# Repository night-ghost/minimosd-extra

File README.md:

# minimosd-extra (russian is at the tail of this file)

Quickstart Guide (c) Johnex
----------------------
1. Download the latest MinimOSD-Extra build here: https://github.com/night-ghost/minimosd-extra/blob/master/osd_latest.zip?raw=true
2. Run the OSD_Config.exe
3. Connect your MinimOSD to your pc making sure you are using an FTDI that has 5V and not 3.3V.
4. After the usb driver is installed, select your COM port in OSD_Config.
5. Click Options -> Update Firmware. Select the latest MinimOsd_Extra_Uni.8XXDV-release.hex file from the "FW_+_Char" folder.
6. This firmware has a built in character set uploader, so just click Options -> Update CharSet. Select the latest character set MinimOSD_2.4.1.X.mcm from the "FW_+_Char" folder. Notice that this MimimOSD-Extra has a custom character set and must be updated if coming from another fork or the original, and some newer versions might require a new version, always check the "FW_+_Char" folder.
7. Set your video mode to Auto if you have different cam types, or select NTSC or PAL if you have just 1 cam and you know it's type or had issues with Auto.
8. Connect your OSD directly to a monitor or to a video transmitter so you can see the OSD output, making sure you don't forget to connect the antenna to the video transmitter before powering it on if you are using that. Click Options -> Load TLog. Select 2015-09-06 18-40-55.tlog from the "FW_+_Char" folder.
9. Set up the screens as you want. Click "Save Tab to OSD" and then click "Start" to run a simulation so you can see how everything looks without having to set up a copter. If something is not right, click "Stop", do the changes, save the config again and click "Start" again to see the new changes.
10. If you encounter that your screen is not centered, change the "Offsets", Left and Top from the config page. You can also move panels away from the edge if your screen gets cropped.

Description

* refactored a bit - now uses much less memory and can use less EEPROM

* also MAX7456 renew doing in VSYNC to get rid of "snow" on screen - like 
in http://forum.rcdesign.ru/f90/thread132831-195.html#post5602416 but on interrupt instead of polling via SPI.

* Also PSTR to all strings

* NEW FEATURES:

* 4 screens instead of 2

* individual control of sign icon of each panel per screen

* voltage, current & RSSI can be used from external pins

* TLOG player in configurator - now settings can be checked without working plane/copter!

* RADAR (like in MiniNAZAosd) and ILS in Horizon, can be enabled individually

* horizon angles can be adjusted, indepentently in PAL and NTSC

* PAL/NTSC detected dynamically - now can use different cameras!

* screen offsets via configurator

* can use additional pins (that can be found on some boards) for measuring 2nd battery current and voltage

* new GPS coords - in one line

* fixed a lot of old bugs of CT

* Any RC channel can be translated to output pin (eg. for cameras switch)

* Setup screen! Some parameters can be adjusted without computer - by RC 

* Panel in CT can be dragged over any point, not only for the upper left corner

* and much more! See [CHANGELOG.md](https://github.com/night-ghost/minimosd-extra/blob/master/CHANGELOG.md)

If you like this project and want to support further development - you can do it! USD
   EUR

changelog in [CHANGELOG.md](https://github.com/night-ghost/minimosd-extra/blob/master/CHANGELOG.md)
some descriptions are in [wiki](https://github.com/night-ghost/minimosd-extra/tree/master/wiki)

fonts:

MinimOSD_2.4.1.x.mcm         - base font
MinimOSD_2.4.1.x-digital.mcm - styled for 7-segment and dotted horizon

Attention! This version is incompatible with the tools from the ArduCam and original MinimOSD-extra!

Discussion forum - http://www.rcgroups.com/forums/showthread.php?t=2591835 (abandoned) http://www.ykoctpa.ru/groups/eye-in-a-sky/forum/topic/minimosd-english-support-thread/#post-9147

/* RUSSIAN */

Быстрый старт

1. Загрузите последнюю версию MinimOSD-Extra отсюда: https://github.com/night-ghost/minimosd-extra/blob/master/osd_latest.zip?raw=true
2. Запустите OSD_Config.exe
3. Подключите MinimOSD на ваш компьютер, убедившись, что вы используете FTDI с напряжением 5V, а не 3.3V.
4. После установки драйвера USB, выберите COM-порт в OSD_Config.
5. Нажмите кнопку Options -> Update Firmware. Выберите последнюю версию файла MinimOsd_Extra_Uni.8XXDV-release.hex из папки "FW_+_Char".
6. Эта прошивка имеет встроенный загрузчик знакогенератора, так что просто нажмите кнопку Options -> Renew CharSet. Выберите последний набор символов MinimOSD_2.4.1.X.mcm из папки "FW_+_Char". Обратите внимание на то, что этот MimimOSD-Extra имеет свой набор символов, и не будет работать с символами из других версий. Поэтому знакогенератор модуля должен быть обновлен, так что всегда проверяйте папку "FW_+_Char".
7. Установите режим видео на Auto, если у вас одновременно различные типы камер, или выбрать NTSC или PAL, если у вас есть только один камера, и вы знаете ее тип.
8. Подключите OSD непосредственно к монитору или видео передатчик, так чтобы увидеть вывод OSD, убедившись, что вы не забыли подключить антенну к видеопередатчику перед включением его. Нажмите кнопку Options -> Load TLOG. Выберите 2015-09-06 18-40-55.tlog из папки "FW_+_Char".
9. Настройте экраны, как вы хотите. Нажмите кнопку "Save Tab to OSD", а затем нажмите кнопку "Start", чтобы запустить моделирование. Теперь вы сможете увидеть как все выглядит на самом деле без необходимости подключать коптер/самолет. Если что-то не так, нажмите кнопку "Stop", сделайте изменения, сохраните конфигурацию и нажмите кнопку "Пуск" снова, чтобы увидеть новые изменения.
10. Если вы обнаружите, что ваш экран не по центру, то можете изменить "Offsets", слева и сверху, на вкладке конфигурации. Можно также перемещать панели подальше от края, если ваш экран обрезан.

Описание отличий

* Отрефакторил, убрав чудовищный расход памяти на хранение всех настроек всех возможных экранов сразу, также 
убрал "регистры" флагов (и все с ними связанное) в пользу хранения вместе с координатами. Ну и по 
мелочи - PSTR, PROGMEM и отказ от ненужных статических массивов. 

* В результате имеем свободных 721 байт вместо 160 в оригинале. 

* Также сделано обновление памяти MAX7456 во время VSYNC дабы избавиться от "снега" на экране из-за помех, по мотивам
http://forum.rcdesign.ru/f90/thread132831-195.html#post5602416 но через прерывание вместо странного поллинга 
через SPI.

* Также сделана регулировка отступов от края экрана через конфигуратор

** НОВЫЕ ВОЗМОЖНОСТИ!

* Объединены самолет и коптер, выбор производится по значению из EEPROM и может МЕНЯТЬСЯ НА ЛЕТУ!

* Уменьшен расход EEPROM в три раза (!). В результате можно задать 4 экрана вместо 2-х и при этом куча свободного места под новые параметры.

* Чтение-запись EEPROM в цикле а не индивидуальными байтами - нет больше длинных "портянок"

* Видимость иконок - обозначений каждой "панели" задается индивидуально, независимо по экранам

* Напряжения, токи и RSSI могут читаться с дополнительных выводов (со сглаживанием по 8 отсчетам),
источник и поправочные коэффициенты задаются в конфигураторе независимо

* Переключение экранов может производиться по внешнему PWM для использования с номерами каналов выше 8

* В авиагоризонте сделаны поправочные коэффициенты (независимые для PAL и NTSC), и добавлен "Радар" (по мотивам МиниНазаОСД). 

* Видимость Радара и ILS задается индивидуально.

* Изменена логика формирования "панелей", так что теперь мелкие панели могут использовать незадействованные области крупных панелей. 
Это позволило отрисовывать радар, ILS и центральный маркер в пределах авиагоризонта

* Переключение PAL/NTSC может производиться "на лету", без перезагрузки - позволяя использовать две камеры разных форматов

* в коде сделан отладочный HEX-дамп прямо на экран

* В конфигураторе сделан плеер TLOG - теперь можно проверить работу OSD без самолета/коптера.

* Смещение экрана относительно синхроимпульсов задается через конфигуратор

* Изменен шрифт для отображения всех новых вкусностей

* Сделан вариант отображения координат GPS в одну строку

* Добавлена возможность вывода любого канала наружу в PWM 

* После всего этого остается свободно 325 байт памяти и 2+к флеша.

* Экран настройки! До арма можно менять некоторые параметры без компьютера - просто с пульта

* Исправлено множество старых багов конфигуратора

* панель в конфигураторе можно таскать за любую точку а не только за левый верхний угол

* и многое другое - смотрите [историю версий](https://github.com/night-ghost/minimosd-extra/blob/master/CHANGELOG_RU.md)

Если вам понравился проект и вы хотите поддержать его дальнейшее развитие - вы можете это сделать 
 USD  
 RUB

история версий в файле [CHANGELOG_RU.md](https://github.com/night-ghost/minimosd-extra/blob/master/CHANGELOG_RU.md)

Шрифты:

MinimOSD_2.4.1.x.mcm         - основной фонт
MinimOSD_2.4.1.x-digital.mcm - стилизация под 7-сегментный индикатор и точечный горизонт

Внимание! Эта версия несовместима с утилитами из оригинальной MinimOSD!

некоторая документация есть в [wiki](https://github.com/night-ghost/minimosd-extra/tree/master/wiki).

Обсуждение - http://www.ykoctpa.ru/groups/eye-in-a-sky/forum/topic/minimosd-novaya-proshivka/

ЛИЦЕНЗИОННОЕ СОГЛАШЕНИЕ (честно потыренное у Ubilling)

Данный программный продукт (далее ПП) распространяется под лицензией GNU GPL v.2 с полностью открытым кодом и полностью бесплатно.
Так было всегда, так и останется. Без компромиссов. THIS IS SPARTA OPENSOURCE!!!
Обрекший себя на использование данного продукта принимает тот факт, что ему никто и ничего не должен.
Вообще никаких гарантий - ни явных ни подразумеваемых. Все работает так как работает.
Перед использованием ПП верующим рекомендуется поставить свечку в храме, атеистам - геморроидальную.
Мы не несем никакой ответственности за хаос, панику, разрушения и апокалипсис, возникшие в процессе эксплуатации. 
Если у вас возникли вопросы - потрудитесь почитать документацию. Если документация не дала ответов о смысле жизни - попробуйте спросить на форуме.
По умолчанию все баги являются фичами, если вы считаете что нашли багу - попробуйте ее использовать в повседневной жизни ну или расскажите нам.
Если у вас есть какая-то хотелка нужная строго вам - вы можете реализовать ее либо самостоятельно и сделать PR на гитхабе, 
либо заказать, либо продолжать хотеть. 
Это намек на то, что бесплатно работать фуллтайм на вас никто не вписывался.

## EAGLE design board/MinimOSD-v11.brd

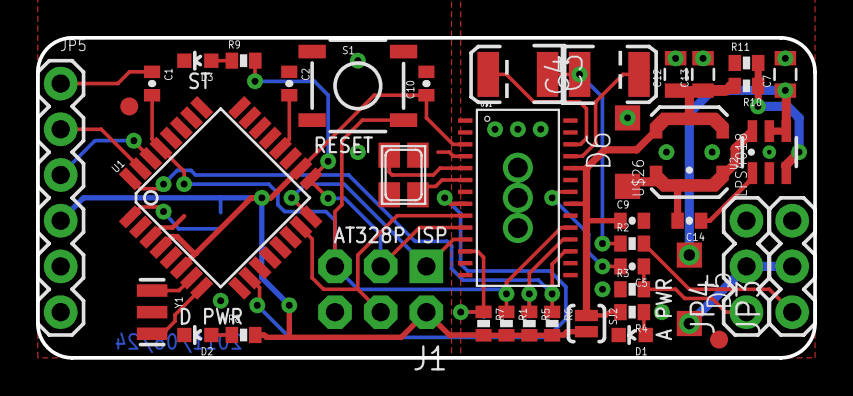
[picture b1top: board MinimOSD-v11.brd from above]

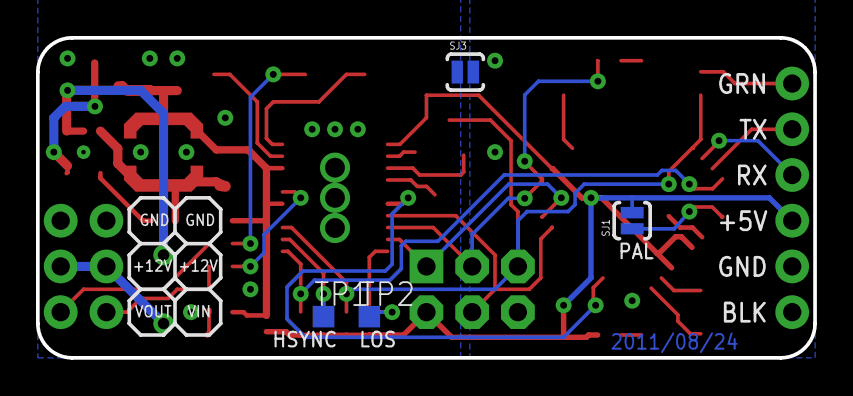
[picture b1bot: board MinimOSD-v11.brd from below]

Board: 4 copper layers, 43.2 x 17.8 mm, 45 parts (4 on the bottom side), 35 nets.

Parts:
C1, C2, C5, C9, C10: 0.1uF; 0402-CAP
C3, C4: 47uF; EIA3528
C7: 1uF; 0805
C12, C13: 4.7uF; 0805
C14: 0.15uF; 0402-CAP
D1, D2: RED; LED-0603
D3: YELLOW; LED-0603
D5: SOD123
D6: MA2YD26; SOD123
J1: AVR_SPI_PRG_6NS; 2X3-NS
JP1, JP2: FIDUCIAL1X2; FIDUCIAL-1X2
JP3, JP4: 1X03
JP5: 1X06
Q1: 27MHz; NX3225
R1: 10k; 0402-RES
R2, R3: 75; 0402-RES
R4, R8, R9: 330; 0402-RES
R5, R6, R7: 1k; 0402-RES
R10: 5.62k; 0402-RES
R11: 1.02k; 0402-RES
S1: TACTILE_SWITCH_SMD
SJ1, SJ2, SJ3: SOLDERJUMPERNO; SJ_2S-NO
TP1, TP2: TPTP12SQ; TP12SQ
U1: ATMEGA328P; TQFP32-08
U2: LM2842Y; MK06A
U$1: MAX7456; TSSOP28
U$26: LPS4018
Y1: 16MHz; RESONATOR-SMD

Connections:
5V: C10.1, J1.2, JP5.4, R1.2, R5.2, R6.2, R7.2, R8.2, SJ1.2, SJ2.2, U1.4, U1.6, U1.18, U$1.3
AGND: C7.2, C9.2, C12.2, C13.2, D1.C, D6.A, JP3.3, JP4.3, R3.1, R11.1, SJ3.1, U2.2, U$1.20, U$1.23
AVDD: C9.1, C12.1, C13.1, R4.2, R10.2, SJ2.1, U$1.21, U$1.24, U$26.B
DTR: C1.1, JP5.1
GND: C2.1, C10.2, D2.C, D3.C, J1.6, JP5.5, JP5.6, S1.1, S1.2, SJ3.2, U1.3, U1.5, U1.21, U$1.4, Y1.2
HSYNC: R5.1, TP1.TP, U$1.18
LOS: R7.1, TP2.TP, U$1.12
MISO: J1.1, U1.16, U$1.11
MOSI: J1.4, U1.15, U$1.9
unnamed: Q1.4, U$1.6
unnamed: C2.2, U1.20
unnamed: U1.7, Y1.1
unnamed: U1.8, Y1.3
unnamed: Q1.2, U$1.5
unnamed: C3.A, U$1.26
unnamed: C4.A, U$1.25
unnamed: C3.C, C4.C, R2.1
unnamed: C5.2, U$1.22
unnamed: D1.A, R4.1
unnamed: D2.A, R8.1
unnamed: D3.A, R9.1
unnamed: C7.1, D5.C, U2.4, U2.5
unnamed: C14.1, U2.1
unnamed: C14.2, D6.C, U2.6, U$26.A
unnamed: R10.1, R11.2, U2.3
PAL: SJ1.1, U1.1
RAW: D5.A, JP3.2, JP4.2
RESET: C1.2, J1.5, R1.1, S1.4, U1.29, U$1.19
RXI: JP5.3, U1.30
SCK: J1.3, R9.2, U1.17, U$1.10
SSOSD-IN: U1.10, U$1.8
TXO: JP5.2, U1.31
VIN: C5.1, JP4.1, R3.2
VOUT: JP3.1, R2.2
VSYNC: R6.1, U1.32, U$1.17

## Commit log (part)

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2014-03-13 New charset
2014-04-03 Copter: Home Alt -> Relative altitude (from VFR_HUD message) Alt -> GPS reported altitude
2014-04-21 CT Tool: Bug fix uploading charset in newer fw versions
2014-04-29 Copter: Only allow showing flight summary if traveled distance greater than 50 meters
2014-05-08 Copter added new flight modes: flip, auto tune, hybrid
2014-05-13 CT Tool: New automated CT Tool upgrade - In development
2014-11-27 -WP arrow fix for latest arduplane -Alt error fix on tune panel
2014-11-28 Added character uploading FW
2014-11-30 Edited wiki page Charset through web user interface.
2015-02-03 Before transfer to GIT
2015-04-02 added usage of auxilary input pins int in lot of places replaced with uint8_t some font redesign and new visual elements
2015-04-02 updated font and compiled .HEX
2015-04-07 refactored configurator! No more '30', '18' and other mystical numbers - they are now global constants. Number of screens can be easily changed via 'npanels' without any code change. Removed "generat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
2015-04-09 first step of EEPROM reorganization
2015-04-21 now it works!
2015-04-23 RADAR from naza osd
    new cool fonts
2015-04-24 screen offsets now a via config tool
2015-04-27 final clearance
2015-07-10 PAL/NTSC live change now working!
    removed BUG with GPS2 panel
2015-07-15 readme changed
2015-10-15 enabled translation of PWM from RC6-RC8 to external pin
2015-12-13 fixed bug with formatting in configuration applet Flight results panel now can be on any screen Class SingleSerial - uses ~500 bytes less flash than FastSerial other space optimizations - now free 4,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
    в конфигураторе исправлен баг с форматированием
    панель сводки сделана равноправной и ее можно назначить на любой экран
    Класс SingleSerial - на ~500 байт меньше чем FastSerial
    прочая оптимизация размера кода - теперь свободно 4.5к флеша
2015-12-28 serial buffer counters reduced to uint8_t
2016-01-28 PWM output working! binary recompiled with GCC 5.3
2016-01-28 decorative removal of old code
2016-01-29 now it compiles
2016-01-29 proportional increment in setup
2016-01-30 OSD_Config rebuild by MS VS
2016-02-01 fixed bug with "long distances" display
2016-02-02 adding NOINLINE to some functions saves ~400 bytes
2016-02-02 fixed CT startup bug
2016-02-24 working SETUP & fixed bugs
2016-02-26 automatic UAVtalk IDs generation
2016-03-09 v813:
    HUD borders can be turned off
    RADAR point can show track (3 points) - requires charset 2.4.1.2
    RSSI values now is 2 bytes and has no 255 limit
2016-03-11 created manlink-only HEX MinimOsd_Extra_Uni.813DV-MAVlink-release.hex
2016-03-13 v814
    fixed bug "no input data"
    fixed wrong pitch
2016-03-16 v815
    fixed bug with battery panel sizes
2016-03-18 default panel's placement changet to panels don't overlaps
2016-03-18 corrected CRC issue in UAVtalk more space optimizations
2016-03-23 support for new APM_Plane modes - quad-plane new parameters in Setup screen much more space optimizations preliminary support for AutoQuad MAVlink dialect preliminary support for CleanFlight/MWII pro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
2016-03-24 v816:
    Walkera telemetry output (for DEVO RX705/RX707 receivers) now working!
    Support of CleanFlight/MWII protocol (untested)
    Support of AutoQuad's MAVlink dialect (untested)
    support for new APM_Plane modes for quad-plane
2016-03-25 filtered out GCS messages, translated by Copter 3.3+ and plane 3.4+
2016-03-26 fixed small bug in MAVlink handling
2016-03-27 binaries for v817
2016-03-28 do it compiles via MAKE
2016-03-29 changed logick of calculation of battery percentage
2016-03-29 Single Serial Submodule Updated Command: git submodule update --remote --merge
2016-03-30 v819
2016-03-30 CT: removed MsgBox'es from EEPROM utils CT: TLig player stops when COMport used
    removed delay() in setup()
2016-04-01 v821 * fixed buk with NTSC in CT * better UAVtalk & mwii syncronization * PWM_IN interrupt enabled only if used * some cleanup * ZIP file for download all needed
2016-04-02 v823 * add new flag to all panels that turns on "alternate" mode for some panels * WindSpeed, Airspeed and Groundspeed in Alternate mode shows speed on m/s instead of km/h * new charset to show m/s
2016-04-05 Quick Start on Readme
2016-04-08 v826
    * MAVlink message scrolled if length more than screen width
2016-04-10 Update README.md
    Fix latest link.
2016-04-13 some changes in CT Settings tab
2016-04-18 v828
    * sensor has "pulse mode" checkbox
    * some optimizations
2016-04-19 some bugfixes with RSSI in CT
2016-04-22 created DEBUG version
2016-04-25 v831
    * screen switch in rotation mode can be done only once
2016-05-10 v833
    * reserved space for sign for climb rate
2016-05-13 rename 'FW & Char' folder to 'FW_+_Char'
2016-05-13 v836 * support for LTM telemetry protocol (untested)
2016-05-17 * fixed bug with Message panel
2016-05-20 v839 * fixed Vertical Speed panel broken in v838
2016-05-23 changes in Readme
2016-05-25 * panelRose modification
2016-05-26 v842 * one good man from GCC team told me two "secret" (not mentioned in GCC --help) optimization flags so we now has ~1Kbyte of free space! * thanks above - added 2nd, 3rd and 4th alternate checkbox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
2016-05-27 v843 * 3DR modem RSSI can be used as RSSI source * additional fields in flight results - current, vertical speed up & down * support for GPS-less setup: Alt and Groundspeed works without GPS * flight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
2016-05-30 v845 * fixed bug in ChannelStatus panel * CT clears message after 10s
2016-05-30 * fixing panHDOP and panGPSats
2016-06-01 v847 * fixed NTSC inconsistency with the CT * removed % from panRSSI in CT * added ability to exclude MAVlink from build * all telemetry protocol's files moved to 'protocols' folder * fixed panel siz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
2016-06-02 uploaded CT sources
2016-06-03 added debug version
2016-06-05 Add buttons to clear a screen and copy another screen.
2016-06-07 Add ui_mode to Panels
2016-06-09 fixed bug in CT with reading panel Scale from OSD
2016-06-09 Reorganize X and Y UI controls
2016-06-10 fixed bug with flickering panels
2016-06-10 again fixed framerate bug
2016-06-14 v853 * strings now are working! And Channel State panel uses first 5 of them
2016-06-15 v856 *fixed bug with panel's properties visibility
2016-06-21 v857 * fixed bug with panel selection in CT * complementary filter of panEff changed from 1/10 to 1/100 * a try to change Horizon behavior for large banks (>70grad) * minor fixes
2016-06-29 * ILS now allows plane to come to runway from opposite direction * fixed bug in ILS with HUD size * when landing margers are not visible ILS now show arrows to help find smaller turn * some size opti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
2016-07-01 v858 * fixed some CT bugs * localisation support! lang.txt file in EXE's folder, * support of timed screen switch (untested) * file default.osd loaded at startup if present * fixed bug with reverse R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
2016-07-01 v860 * MAVLink don't loses sync on CRC errors * time counted for "no data" state
2016-07-04 v861 * some bugfixes
2016-07-05 * fixed stick direstions in Setup * fixed sensors in Setup
2016-07-12 v865 * calculates adequate stream rate for current COM-port baudrate. * detects overloaded datastreams and (if TX connected) tries to re-request them at less rate. * minor fixes * CT shows TLOG time
2016-07-13 v867 * reversed roll in horizon AKA Russian HUD
2016-07-18 v869 * support for copter's Brake and Throw modes
2016-07-20 v870 * unknown new modes shown as numbers but not as screen garbage
2016-07-25 v872 * added detected port speed to "no data" screen
2016-07-27 added MinimOsd_Extra_Uni.873DV-MAVLINK-release.with_bootloader.hex
2016-08-01 v875 * UAVtalk works again! * fixed underflow bug in panRose * fixed lagre pitch horizon behavior
2016-08-04 v876 * UAVtalk uses BaroAlt when no GPS. * fixed flight time counting * fixed RussianHUD on startup screen
2016-08-09 v877 * new Power panel which shows mean consumed power (smoothing by complementary filter 1:10) * maximal power added to flight results (FlightData panel) * all complementary filters are unified * tr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
2016-08-22 v879 * fixed Voltage and Altitude for UAVtalk * added Temperature (by Baro) for UAVtalk * if MAX7456 loses VSYNC interrupts then OSD switch to old-style refresh by timer - snow on scren is better tha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
2016-08-23 Add files via upload
    -Direction arrows redraw
    -Some changes to dashes in horizon symbols
2016-08-29 * README.md split to README.md,CHANGELOG.md and CHANGELOG_RU.md * all the above files copied to Released folder on each commit
2016-09-01 * added UAVTalk-debug binary
2016-09-05 Coding style issues
    - Removing trailing whitespaces.
    - Tabs converted to whitespaces.
2016-09-10 Revert "Fix NTSC Designer"
    This reverts commit a6b417d5ab8283d063f37c9141e0aaba490aca9d.
2016-09-10 remove usage of PAL related variables
2016-09-17 commited right version of CT
2016-09-20 try to upload
2016-09-28 small typo fix
2016-10-03 added HEX with Walkera telemetry support - MinimOsd_Extra_Uni.887DV-MAVLINK+Walkera-release.hex
2016-10-12 added License in Russian part of Readme
2016-10-21 v890 * added recent MAVlink 1.0 massages * new panels - date & time. Works only in recent ArduPilot versions! * panel Home Direction now has a angle in numerical form * added filter to RSSI panel * a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
2016-11-03 a little black magic - and we again have ~300 bytes of a free flash. Magic can be seen in compat.h
2016-11-08 Variometer panel sample in CT
2016-11-11 updated CT to support 3000 RSSI value
2016-11-13 v897 * fixed efficiency
2016-11-13 added issue template
2016-11-17 v901 * added "*4" checkbox to variometer
2016-11-18 dropped packet count changed from 5 to 10
2016-11-18 903 * fixed bug with vario zero position
2016-11-24 v905 * fixed NTSC horizon bug * added checkbox in RadarScale to select UAV arrow direction
2016-12-07 v807 - TEST VERSION! * removed usage of nested interrupts
2016-12-08 v909 * fixed bug with MAVlink message
2016-12-13 v911 - THE TEST VERSION!!! * another try to work on myairbot's board and not spoil regular boards
2016-12-27 v913 *added new panel - motors output
2016-12-30 v914 * separated panels for coordinates Lat and Lon
2017-01-12 v916 * panAlt can use alternate altitude source
2017-01-14 v918 * a try to run on airbot's board - thanks vierfuffzig!
2017-03-20 v921 * fixed bug in parsing MAV_BATTERY2 message
2017-03-21 v923 fixed size issue
2017-03-24 rebuilt binaries
2017-03-27 v925 * font uploader moved out from main firmware. Use Character_Updater_FW.hex instead. * HeartBeat packets generated only if 3DR RSSI selected
2017-04-06 v927 * added EEPROM reading via MAVlink * fixed bug with "Reading param 12" in MP
2017-04-16 v930 * fixed startup hang from v929
2017-04-27 add binariy for 644
2017-04-27 v931 * added baudrate setting for NMEA protocol
2017-05-02 v932 * debug version
2017-05-05 added support for 2nd UART on ATmega644
2017-05-06 Added by200 rotation functionality.
    this is a way overdue port of my patch to the original minimosd-extras:
    https://github.com/diydrones/MinimOSD-Extra/compare/master...marcmerlin:remove_ms_rot?expand=1
    I had to disable USE_AUTOSWITCH code due to the code size issue.
    Feel free to re-enable and disable/remove something else.
    Technically my code makes the mode switch rotation code obsolete,
    because you can use it instead of the mode switch detection, and it
2017-05-07 Revert some changes for an easier merge with upstream.
2017-05-10 fixed wp distance
2017-05-11 v935
    * \r\n\ for NMEA protocol
2017-06-04 Fix some issues and errors I found
    NMEA.h still do not work correct and do not shows correct Lan/Lon and are not usable.
    It seems function "GPS_calc_longitude_scaling()" do not work correct too.
2017-06-09 LAT and LON are corected
2017-06-20 v938 * Preliminary support for PX4 firmware
2017-10-23 support for bi-directional MAVlink configuration in CT
2017-12-19 v940
    * fully working binaries - fixed GCC's bug in OSD::write_S
    * removed MAVlink font upload for ATmega328 boards
2017-12-21 fixed CT version
2017-12-26 v942 * fixed bug with empty screen * fixed bug in climbRate * changed variometer's scale
2018-01-30 fix for motor_state
2018-02-07 v943 * removed integer filtration of voltage in favor of built-in filtering in float * used filtered voltages for warnings
2018-03-06 fixed compatibility with new fonts in slave build
2018-03-17 MWII fixes to bat voltage and roll/pitch data
2018-04-07 increased priority of HomeDir and HomeDist panels
2018-04-27 removed double grad_to_sect function call
2018-05-21 fixed bug in HomeDir panel
2018-05-22 Actualize of MSP_STATUS message
2018-06-01 v946 - MWii fixes from BondarenkoA
